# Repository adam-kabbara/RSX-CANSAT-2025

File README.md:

# RSX CanSat 2T4-2T5 Designs 

<div style="display: flex; gap: 20px; align-items: center;">

</div>
<br>

This repository is designed to manage the files made by the CanSat Team under the Robotics for Space eXploration (RSX) design team at the University of Toronto. 

**Competition Team Members:**
- Adam Kabbara | CanSat Team Lead
- Arthur Goetzke-Coburn | Mechanical Team Lead
- Daniel Yu | Electrical Team Lead
- Luke Watson | Software Team Lead
- Gianluca Ceccacci | Mechanical Team Member
- Nour Barsoum | Electrical Team Member
- Angelique Liao | Software Team Member
- Alexey Albert | Mechanical Team Member
- Robert Saab | Electrical Team Member

**CanSat Competition:**
- 📅 June 5-8, 2025
- 📍 Monterey, Virginia, United States
- 📃 [Mission document](CanSat_Mission_Guide_2025e.pdf)

**Competition Deliverables:**
- 🏆 95.87725%: [CanSat 2025 Winners](https://cansatcompetition.com/winners.html)
- 📋 Scoresheet: [TBA]()
- 💾 Mission Data: [Team #3114 Mission Data](competition_documentation/3114_mission_data_cansat_2025.csv.xlsx)
- 📝 Preliminary Design Review: [Team #3114 PDR](competition_documentation/deliverables/Cansat2025_3114_PDR.pdf)
- 🛠️ Critical Design Review: [Team #3114 CDR](competition_documentation/deliverables/Cansat2025_3114_CDR.pdf)
- 🌡️ Environemental Testing Document: [Team #3114 ENV](competition_documentation/deliverables/Cansat2025_3114_Mission_Operations_Manual.pdf)
- 🗂️ Mission Operations Manual: [Team #3114 MOM](competition_documentation/deliverables/Cansat2025_3114_Mission_Operations_Manual.pdf)
- 🛰️ Post Flight Review: [Team #3114 PFR](competition_documentation/deliverables/Cansat2025_3114_PFR.pdf)
- Note: The links above may be outdated.

**Competition Results:**
- 🗺️ 5th Place Internationally!
- 🌎 1st in North America!
- 🍁 1st in Canada!

## Folder Organization

**Calculations:**
<br> Python functions and calculations for sizing inductors and capacitors in a power electronics circuit, including formulas for inductor DC current, ripple current, peak current, and minimum capacitor value, with example calculations and printouts.

**Circuit Design:**
<br>This folder contains all the KiCad printed circuit board (PCB) designs our team has created. It also includes each PCB's related schematic, layout, and gerber files with associated custom KiCad symbols, footprints, and 3D models.

**Competition Documention:**
<br>All deliverables, team logos, and full results from the 2025 CanSat Competition in Monterey, Virginia, USA!

**Full Sensor Setup:**
<br>Initial code used to connect all payload sensor electronics together for testing before integration with full software telemetry.

**Ground Station/Telemetry Source:**
<br>Mission specific operations on payload and ground station.

**PID:**
<br>The code, notebooks, and scripts for developing, testing, and simulating PID control algorithms and sensor integration for the CanSat project.

**PFR Plots:**
<br>Contains Python scripts and output images for generating 2D and 3D plots of CanSat mission and sensor data, including GPS, altitude, and other telemetry visualizations for post-flight review and analysis.

**Sensor Testing:**
<br>All sensors used on our CanSat are tested separately using an ESP32-WROOM-32D Dev Module microcontroller. This folder contains all related information regarding the tests completed on these sensors including past designs, schematics, pin connections, and code.

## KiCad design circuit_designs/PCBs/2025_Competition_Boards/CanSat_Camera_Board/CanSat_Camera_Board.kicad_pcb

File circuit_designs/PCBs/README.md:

# 2025_Competition_Boards
This folder contains a snapshot of all the schematics, boards, and gerber files of the boards taken to the 2025 CanSat Competition.

# Final_Versions
This folder contains the entire KiCad PCB projects of all three boards inclduing improvements made after competition.

# Old_Versions
This folder contains the entire KiCad PCB projects all three boards before technical review. Most of the stitched VIAs are incorrect.

# Power_Management_Prototypes
This folder contains the KiCad projects of initial buzzer and power management board designs. All were later combined into the CanSat_Power_Management_Board.

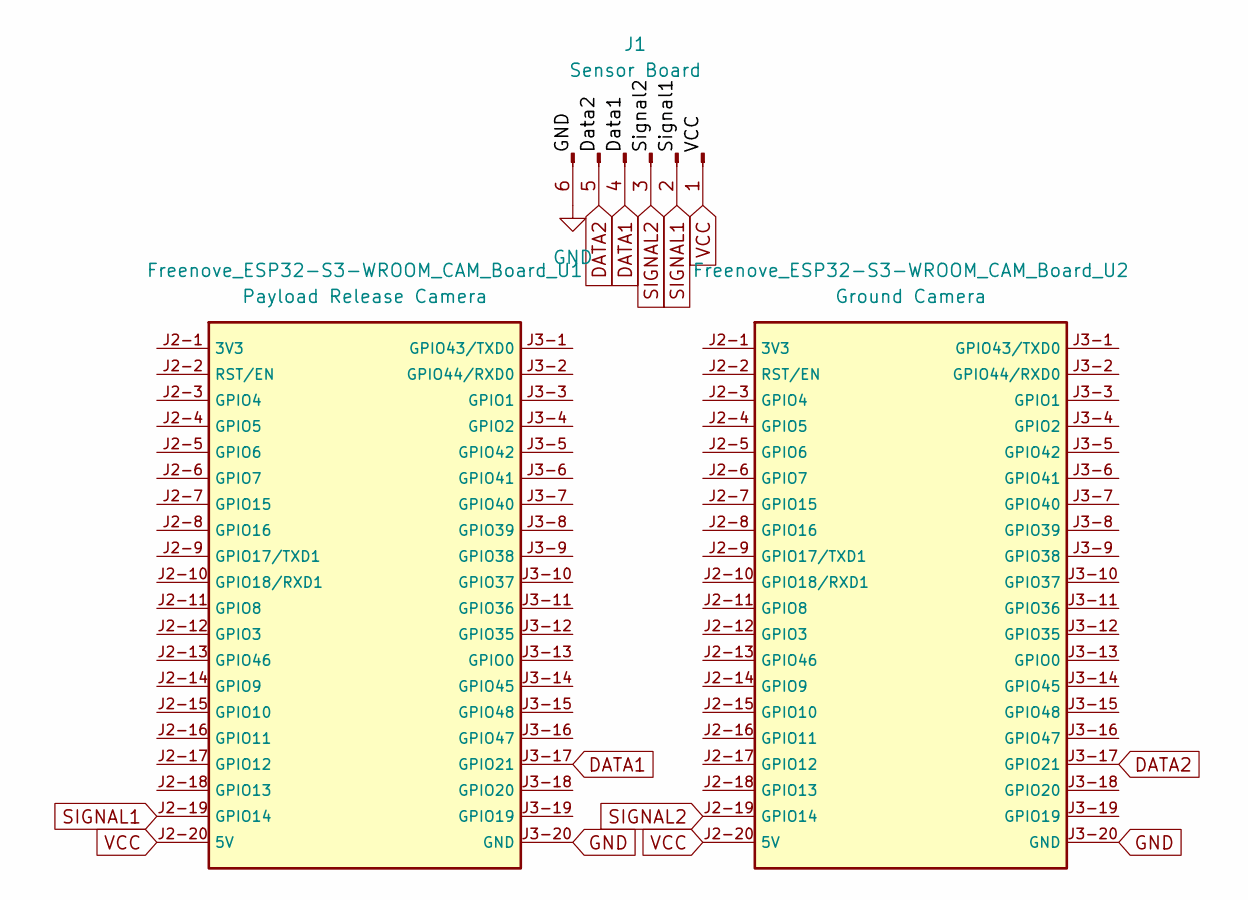
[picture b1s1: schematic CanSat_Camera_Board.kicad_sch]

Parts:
Freenove_ESP32-S3-WROOM_CAM_Board_U1: Payload Release Camera; Freenove_ESP32-S3-WROOM_CAM_Board
Freenove_ESP32-S3-WROOM_CAM_Board_U2: Ground Camera; Freenove_ESP32-S3-WROOM_CAM_Board
J1: Sensor Board; JST_PH_B6B-PH-K_1x06_P2.00mm_Vertical

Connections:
DATA1: Freenove_ESP32-S3-WROOM_CAM_Board_U1.J3-17 (GPIO21), J1.4
DATA2: Freenove_ESP32-S3-WROOM_CAM_Board_U2.J3-17 (GPIO21), J1.5
GND: Freenove_ESP32-S3-WROOM_CAM_Board_U1.J3-20 (GND), Freenove_ESP32-S3-WROOM_CAM_Board_U2.J3-20 (GND), J1.6
SIGNAL1: Freenove_ESP32-S3-WROOM_CAM_Board_U1.J2-19 (GPIO14), J1.2
SIGNAL2: Freenove_ESP32-S3-WROOM_CAM_Board_U2.J2-19 (GPIO14), J1.3
VCC: Freenove_ESP32-S3-WROOM_CAM_Board_U1.J2-20 (5V), Freenove_ESP32-S3-WROOM_CAM_Board_U2.J2-20 (5V), J1.1

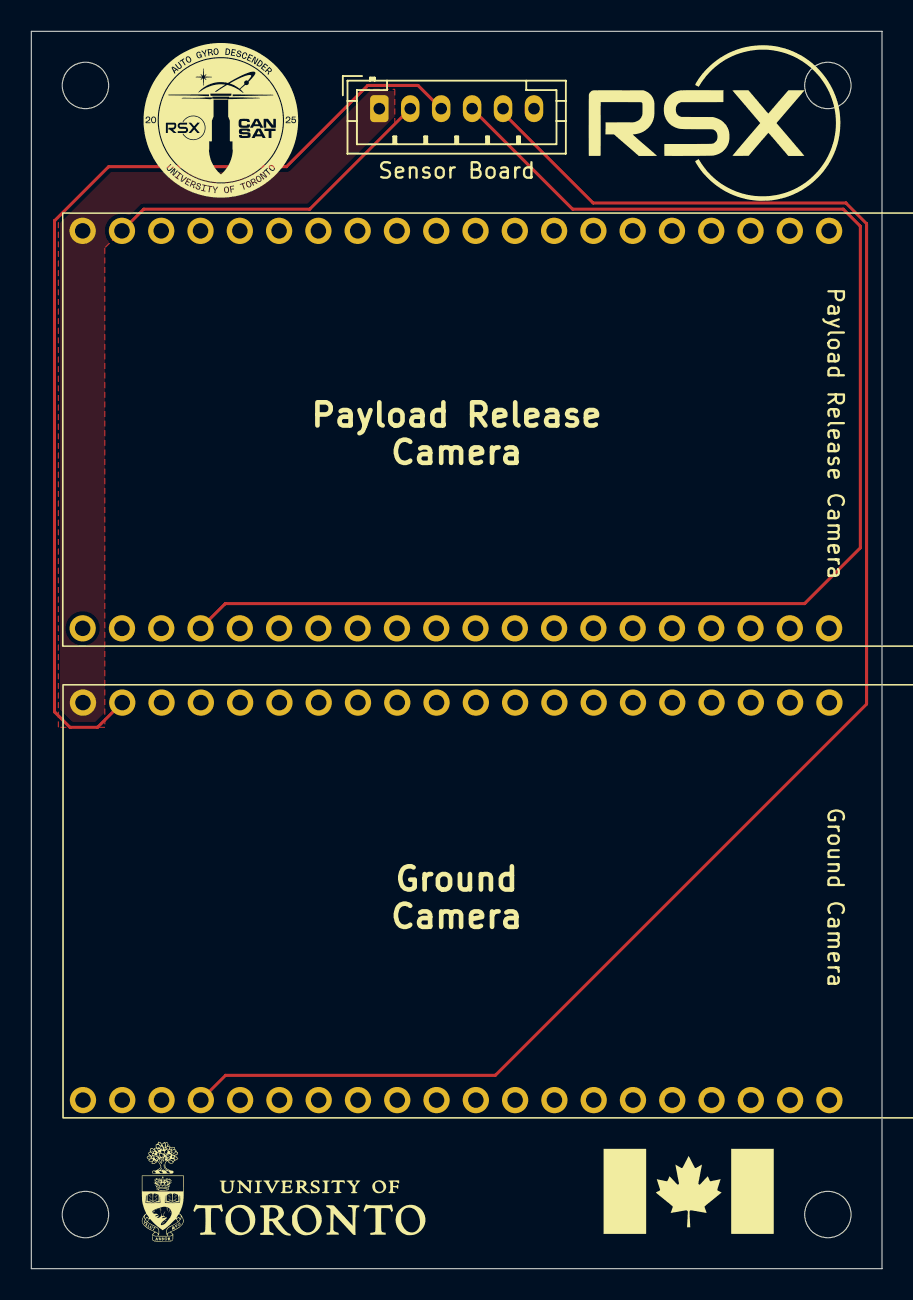
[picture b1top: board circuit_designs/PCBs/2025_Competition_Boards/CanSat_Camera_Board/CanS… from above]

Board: 2 copper layers, 55.0 x 80.0 mm, 3 parts (0 on the bottom side), 6 nets.

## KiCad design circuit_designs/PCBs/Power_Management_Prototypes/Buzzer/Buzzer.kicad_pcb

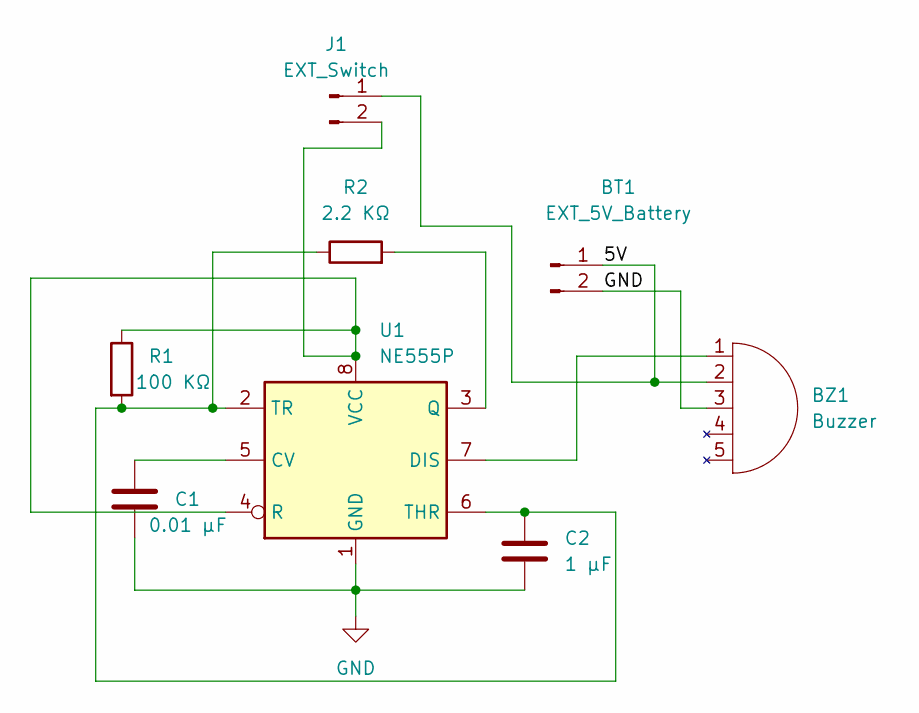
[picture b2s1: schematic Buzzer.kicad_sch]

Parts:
BT1: EXT_5V_Battery; External_Connection_2pin
BZ1: Buzzer; Buzzer_Connection
C1: 0.01 μF; CP_Axial_L11.0mm_D5.0mm_P18.00mm_Horizontal
C2: 1 μF; CP_Axial_L10.0mm_D6.0mm_P15.00mm_Horizontal
J1: EXT_Switch; External_Connection_2pin
R1: 100 KΩ; R_Axial_DIN0207_L6.3mm_D2.5mm_P10.16mm_Horizontal
R2: 2.2 KΩ; R_Axial_DIN0207_L6.3mm_D2.5mm_P10.16mm_Horizontal
U1: NE555P; DIP-8_W7.62mm

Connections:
/5V: BT1.1, BZ1.2 (5V), J1.1
GND: BT1.2, BZ1.3 (G), C1.2, C2.2, U1.1 (GND)
unnamed: BZ1.1 (Aux), U1.7 (DIS)
unnamed: J1.2, R1.1, U1.4 (R), U1.8 (VCC)
unnamed: C1.1, U1.5 (CV)
unnamed: R2.2, U1.3 (Q)
unnamed: C2.1, R1.2, R2.1, U1.2 (TR), U1.6 (THR)

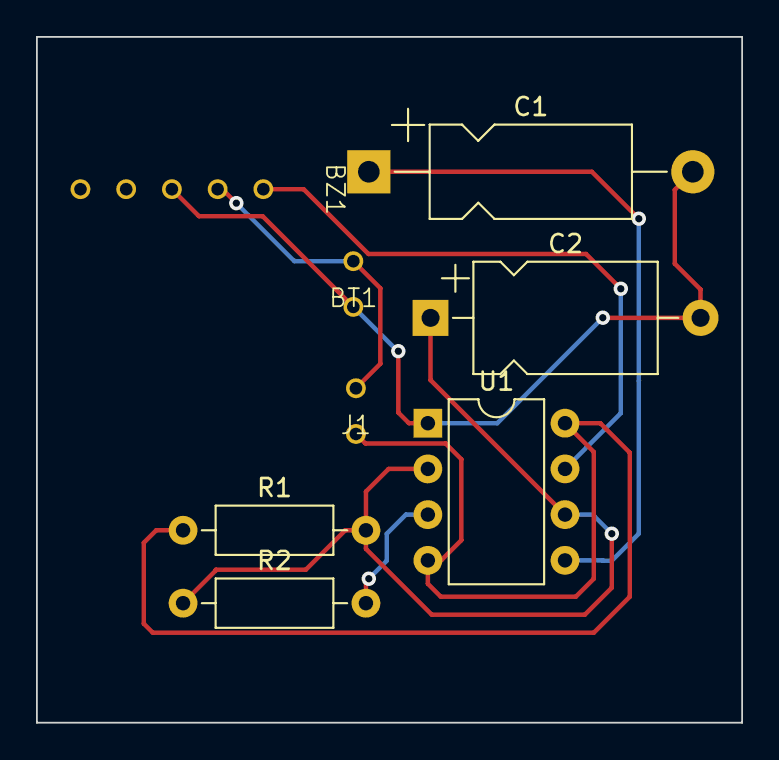
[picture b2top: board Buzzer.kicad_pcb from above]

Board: 2 copper layers, 39.2 x 38.1 mm, 8 parts (0 on the bottom side), 7 nets.

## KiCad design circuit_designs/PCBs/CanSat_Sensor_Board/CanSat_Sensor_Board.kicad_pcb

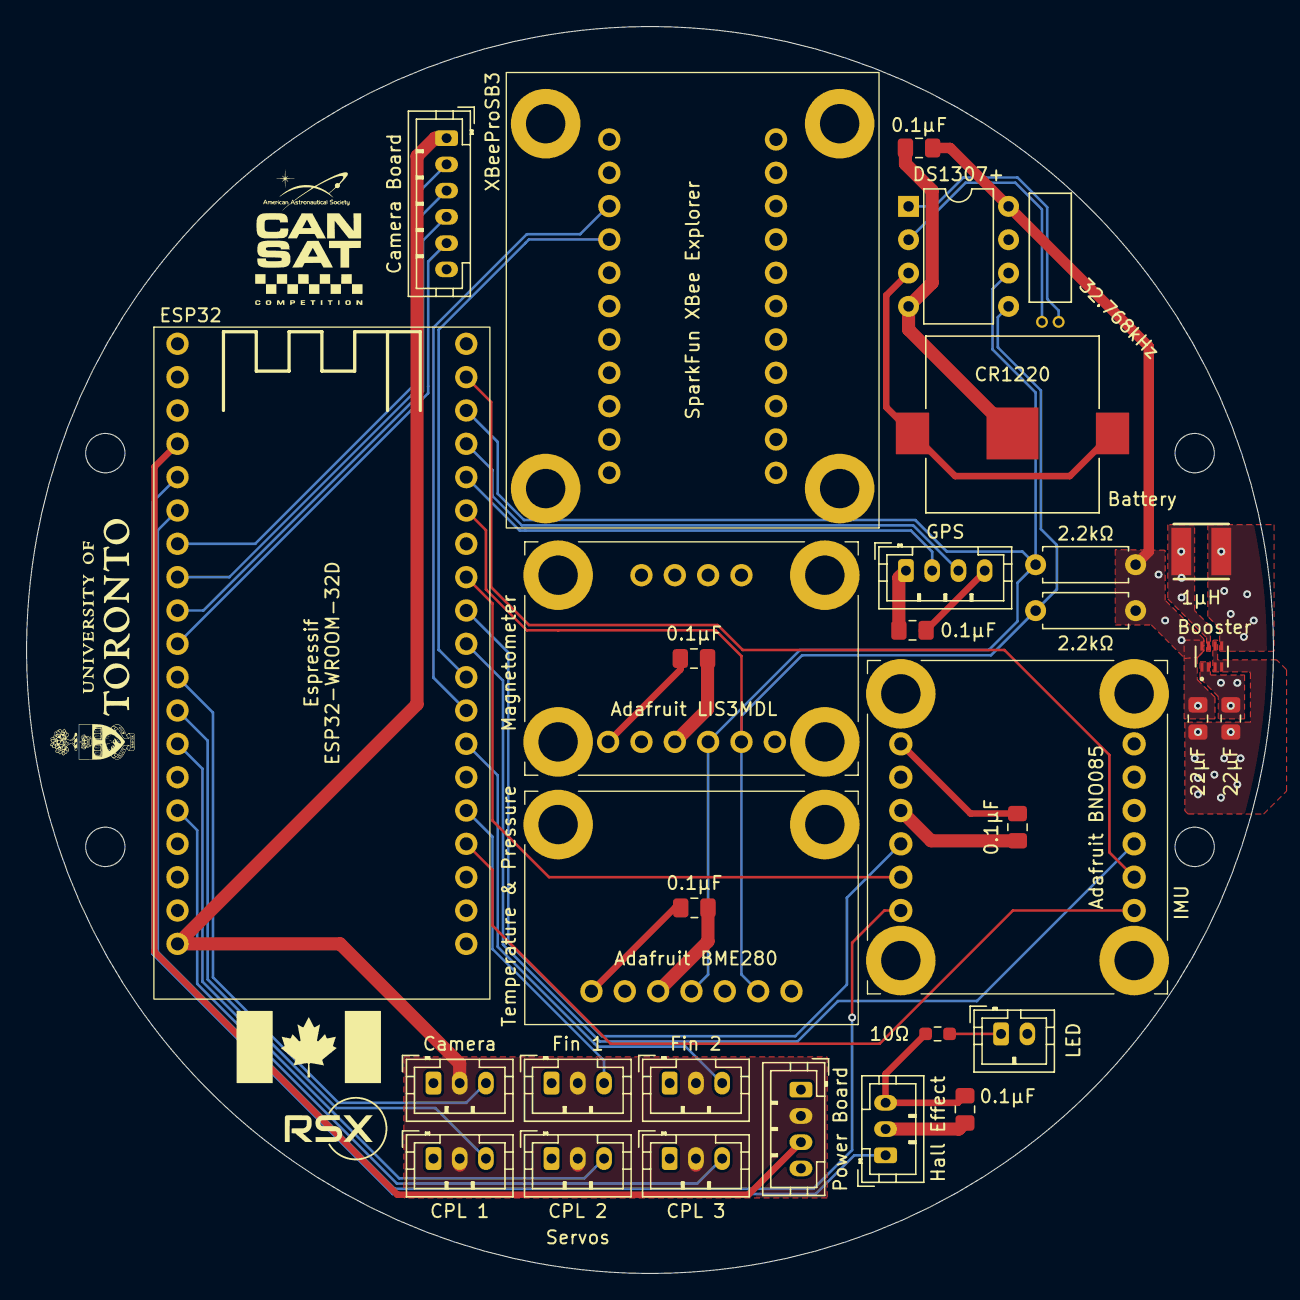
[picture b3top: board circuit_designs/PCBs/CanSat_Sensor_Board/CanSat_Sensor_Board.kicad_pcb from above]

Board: 4 copper layers, 95.0 x 95.0 mm, 32 parts (0 on the bottom side), 33 nets.

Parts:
2894TR_U7: Battery; BAT_2894TR
Adafruit_BME280_STEMMA_QT_U3: Temperature & Pressure; Adafruit_BME280_STEMMA_QT
Adafruit_BNO085_U5: IMU; Adafruit_BNO085
Adafruit_LIS3MDL_U4: Magnetometer; Adafruit_LIS3MDL
C1, C2, C3, C4, C5, C6: 0.1μF; C_0805_2012Metric_Pad1.18x1.45mm_HandSolder
C7, C8: 22μF; C_0805_2012Metric_Pad1.18x1.45mm_HandSolder
DS1307+_U6: DS1307+; DIP-8_W7.62mm
ESP32-DEVKIT-32_U1: ESP32; ESP32-WROOM-32D_Dev_Board
J1: Power Board; JST_PH_B4B-PH-K_1x04_P2.00mm_Vertical
J2: Camera Board; JST_PH_B6B-PH-K_1x06_P2.00mm_Vertical
J3: Hall Effect; JST_PH_B3B-PH-K_1x03_P2.00mm_Vertical
J4: GPS; JST_PH_B4B-PH-K_1x04_P2.00mm_Vertical
J5: LED; JST_PH_B2B-PH-K_1x02_P2.00mm_Vertical
J6: Fin 1; JST_PH_B3B-PH-K_1x03_P2.00mm_Vertical
J7: Fin 2; JST_PH_B3B-PH-K_1x03_P2.00mm_Vertical
J8: Camera; JST_PH_B3B-PH-K_1x03_P2.00mm_Vertical
J9: CPL 1; JST_PH_B3B-PH-K_1x03_P2.00mm_Vertical
J10: CPL 2; JST_PH_B3B-PH-K_1x03_P2.00mm_Vertical
J11: CPL 3; JST_PH_B3B-PH-K_1x03_P2.00mm_Vertical
R1: 10Ω; R_0603_1608Metric_Pad0.98x0.95mm_HandSolder
R2, R3: 2.2kΩ; R_Axial_DIN0207_L6.3mm_D2.5mm_P7.62mm_Horizontal
SparkFunXBeeExplorer_U2: XBeeProSB3; SparkFun_XBee_Explorer_Regulated
TPS610333DRLR_U8: Booster; SOT-5X3-8_DRL_TEX
WE-LQS_4025_L1: 1μH; WE-LQS_4025
Y1: 32.768kHz; XTAL_AB38T-32.768KHZ

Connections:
/3.3V: Adafruit_BME280_STEMMA_QT_U3.1, Adafruit_BNO085_U5.JP1_1 (VIN), Adafruit_LIS3MDL_U4.1, C1.2, C2.1, C3.2, C4.2, C5.2, C7.2, J1.1, J3.3, J4.4, R1.2, SparkFunXBeeExplorer_U2.JP5_10 (3.3V), TPS610333DRLR_U8.1 (VIN), TPS610333DRLR_U8.2 (EN), TPS610333DRLR_U8.5 (FB), WE-LQS_4025_L1.1
/5V: C6.2, C8.1, DS1307+_U6.8 (VCC), R2.1, R3.1, TPS610333DRLR_U8.8 (VOUT)
/7.4V: ESP32-DEVKIT-32_U1.J2-19 (EXT_5V), J1.2, J2.1, J6.2, J7.2, J8.2, J9.2, J10.2, J11.2
/ADC: ESP32-DEVKIT-32_U1.J2-4 (SENSOR_VN), J1.3
/SW: TPS610333DRLR_U8.7 (SW), WE-LQS_4025_L1.2
GND: 2894TR_U7.N, Adafruit_BME280_STEMMA_QT_U3.3, Adafruit_BNO085_U5.JP1_3 (GND), Adafruit_LIS3MDL_U4.3, C1.1, C2.2, C3.1, C4.1, C5.1, C6.1, C7.1, C8.2, DS1307+_U6.4 (GND), ESP32-DEVKIT-32_U1.J2-14 (GND1), ESP32-DEVKIT-32_U1.J3-1 (GND3), ESP32-DEVKIT-32_U1.J3-7 (GND2), J1.4, J2.6, J3.2, J4.1, J5.2, J6.1, J7.1, J8.1, J9.1, J10.1, J11.1, SparkFunXBeeExplorer_U2.JP5_1 (GND), SparkFunXBeeExplorer_U2.JP5_11 (GND), TPS610333DRLR_U8.3 (MODE), TPS610333DRLR_U8.4 (PG), TPS610333DRLR_U8.6 (GND)
unnamed: Adafruit_BME280_STEMMA_QT_U3.4, Adafruit_LIS3MDL_U4.4, DS1307+_U6.6 (SCL), ESP32-DEVKIT-32_U1.J3-3 (IO22), R3.2
unnamed: Adafruit_BME280_STEMMA_QT_U3.6, Adafruit_LIS3MDL_U4.5, DS1307+_U6.5 (SDA), ESP32-DEVKIT-32_U1.J3-6 (IO21), R2.2
unnamed: Adafruit_BNO085_U5.JP2_6 (CS), ESP32-DEVKIT-32_U1.J3-16 (IO15)
unnamed: Adafruit_BNO085_U5.JP2_5 (DI), ESP32-DEVKIT-32_U1.J3-2 (IO23)
unnamed: Adafruit_BNO085_U5.JP1_4 (SCL), ESP32-DEVKIT-32_U1.J3-9 (IO18)
unnamed: Adafruit_BNO085_U5.JP1_5 (SDA), ESP32-DEVKIT-32_U1.J3-8 (IO19)
unnamed: Adafruit_BNO085_U5.JP1_6 (~INT), ESP32-DEVKIT-32_U1.J2-6 (IO35)
unnamed: Adafruit_BNO085_U5.JP2_4 (~RST), ESP32-DEVKIT-32_U1.J3-10 (IO5)
unnamed: 2894TR_U7.P1, 2894TR_U7.P2, DS1307+_U6.3 (VBAT)
unnamed: DS1307+_U6.1 (X1), Y1.1
unnamed: DS1307+_U6.2 (X2), Y1.2
unnamed: ESP32-DEVKIT-32_U1.J3-15 (IO2), J6.3
unnamed: ESP32-DEVKIT-32_U1.J3-13 (IO4), J7.3
unnamed: ESP32-DEVKIT-32_U1.J2-13 (IO12), J10.3
unnamed: ESP32-DEVKIT-32_U1.J2-15 (IO13), J11.3
unnamed: ESP32-DEVKIT-32_U1.J2-12 (IO14), J9.3
unnamed: ESP32-DEVKIT-32_U1.J3-12 (IO16), SparkFunXBeeExplorer_U2.JP5_9 (DOUT)
unnamed: ESP32-DEVKIT-32_U1.J3-11 (IO17), SparkFunXBeeExplorer_U2.JP5_8 (DIN)
unnamed: ESP32-DEVKIT-32_U1.J2-9 (IO25), J2.4
unnamed: ESP32-DEVKIT-32_U1.J2-10 (IO26), J2.5
unnamed: ESP32-DEVKIT-32_U1.J2-11 (IO27), J8.3
unnamed: ESP32-DEVKIT-32_U1.J2-7 (IO32), J2.2
unnamed: ESP32-DEVKIT-32_U1.J2-8 (IO33), J2.3
unnamed: ESP32-DEVKIT-32_U1.J2-5 (IO34), J3.1
unnamed: ESP32-DEVKIT-32_U1.J3-5 (RXD0), J4.2
unnamed: ESP32-DEVKIT-32_U1.J3-4 (TXD0), J4.3
unnamed: J5.1, R1.1

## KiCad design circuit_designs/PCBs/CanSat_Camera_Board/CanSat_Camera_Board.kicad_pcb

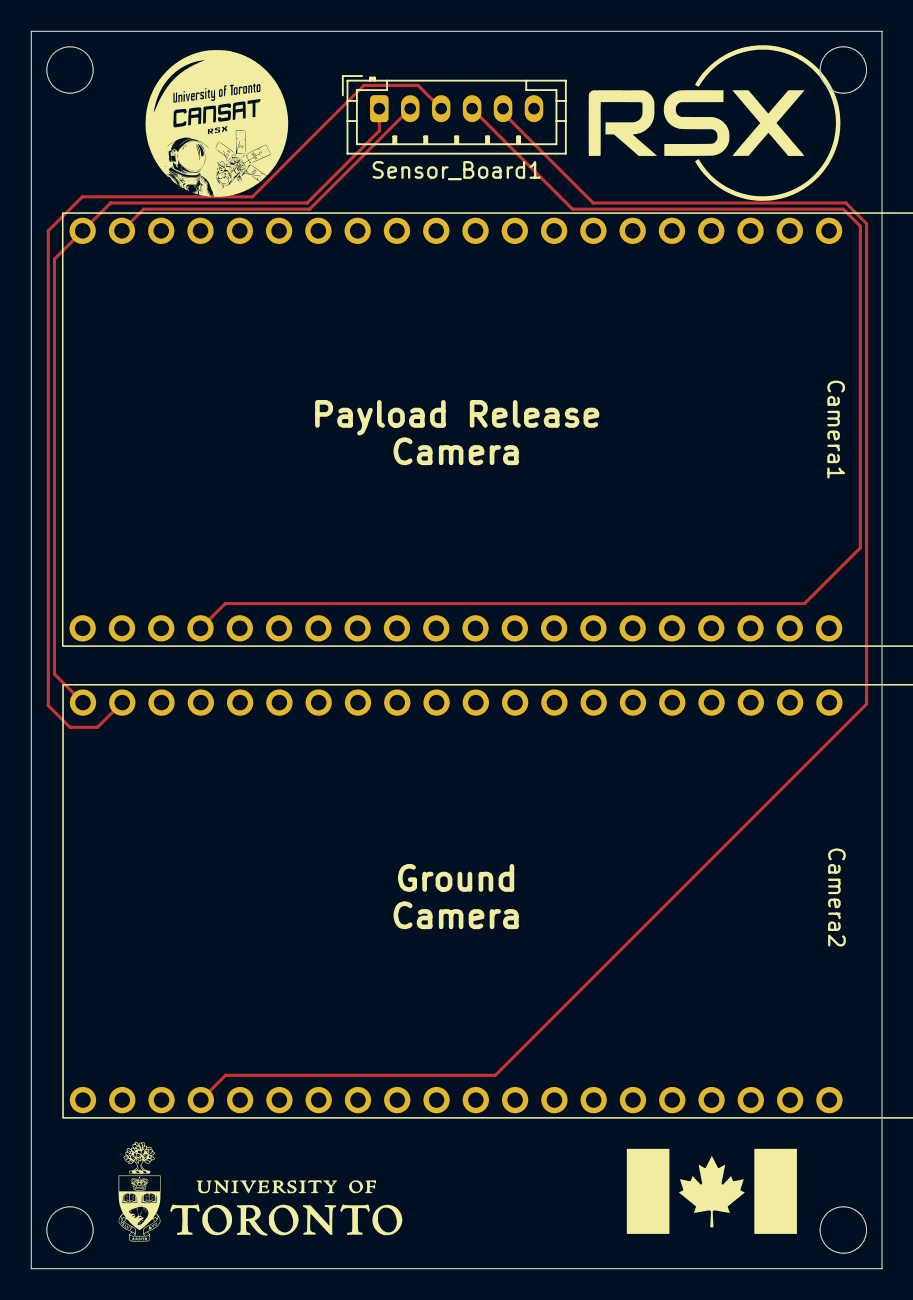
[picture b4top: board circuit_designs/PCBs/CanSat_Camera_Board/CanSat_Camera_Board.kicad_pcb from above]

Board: 2 copper layers, 55.0 x 80.0 mm, 3 parts (0 on the bottom side), 6 nets.

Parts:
Camera1, Camera2: Freenove_ESP32-S3-WROOM_CAM_Board
Sensor_Board1: Conn_01x06_Pin; JST_PH_B6B-PH-K_1x06_P2.00mm_Vertical

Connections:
DATA1: Camera1.J3-17 (GPIO21), Sensor_Board1.4
DATA2: Camera2.J3-17 (GPIO21), Sensor_Board1.5
GND: Camera1.J3-20 (GND), Camera2.J3-20 (GND), Sensor_Board1.6
SIGNAL1: Camera1.J2-19 (GPIO14), Sensor_Board1.2
SIGNAL2: Camera2.J2-19 (GPIO14), Sensor_Board1.3
VCC: Camera1.J2-20 (5V), Camera2.J2-20 (5V), Sensor_Board1.1

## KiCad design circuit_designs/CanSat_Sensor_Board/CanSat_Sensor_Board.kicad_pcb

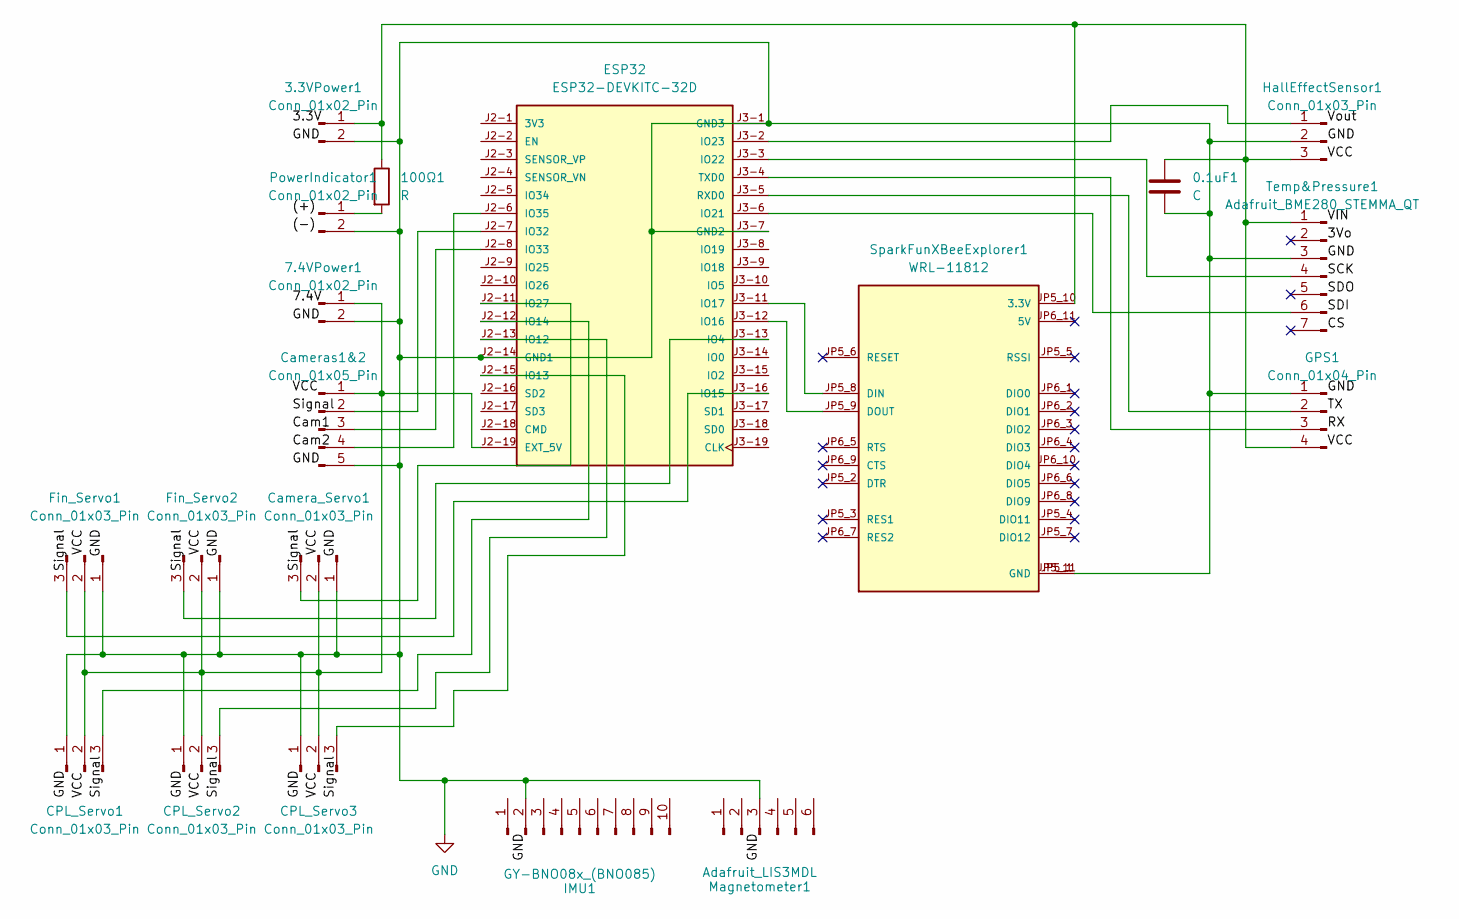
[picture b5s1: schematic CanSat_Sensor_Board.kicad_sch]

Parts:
0.1uF1: C; C_0201_0603Metric_Pad0.64x0.40mm_HandSolder
3.3VPower1, 7.4VPower1: Conn_01x02_Pin; JST_PH_B2B-PH-K_1x02_P2.00mm_Vertical
100Ω1: R; R_Axial_DIN0207_L6.3mm_D2.5mm_P7.62mm_Horizontal
CPL_Servo1, CPL_Servo2, CPL_Servo3: Conn_01x03_Pin; JST_PH_B3B-PH-K_1x03_P2.00mm_Vertical
Camera_Servo1: Conn_01x03_Pin; JST_PH_B3B-PH-K_1x03_P2.00mm_Vertical
Cameras1&2: Conn_01x05_Pin; JST_PH_B5B-PH-K_1x05_P2.00mm_Vertical
ESP32: ESP32-DEVKITC-32D; MODULE_ESP32-DEVKITC-32D; PARTREV V4
Fin_Servo1, Fin_Servo2: Conn_01x03_Pin; JST_PH_B3B-PH-K_1x03_P2.00mm_Vertical
GPS1: Conn_01x04_Pin; JST_PH_B4B-PH-K_1x04_P2.00mm_Vertical
HallEffectSensor1: Conn_01x03_Pin; JST_PH_B3B-PH-K_1x03_P2.00mm_Vertical
IMU1: GY-BNO08x_(BNO085)
Magnetometer1: Adafruit_LIS3MDL
PowerIndicator1: Conn_01x02_Pin; JST_PH_B2B-PH-K_1x02_P2.00mm_Vertical
SparkFunXBeeExplorer1: WRL-11812; MODULE_WRL-11812; PARTREV v21
Temp&Pressure1: Adafruit_BME280_STEMMA_QT

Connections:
GND: 0.1uF1.2, 3.3VPower1.2, 7.4VPower1.2, CPL_Servo1.1, CPL_Servo2.1, CPL_Servo3.1, Camera_Servo1.1, Cameras1&2.5, ESP32.J2-14 (GND1), ESP32.J3-1 (GND3), ESP32.J3-7 (GND2), Fin_Servo1.1, Fin_Servo2.1, GPS1.1, HallEffectSensor1.2, IMU1.2, Magnetometer1.3, PowerIndicator1.2, SparkFunXBeeExplorer1.JP5_1 (GND), SparkFunXBeeExplorer1.JP5_11 (GND), Temp&Pressure1.3
unnamed: 0.1uF1.1, 3.3VPower1.1, 100Ω1.1, GPS1.4, HallEffectSensor1.3, SparkFunXBeeExplorer1.JP5_10 (3.3V), Temp&Pressure1.1
unnamed: 7.4VPower1.1, CPL_Servo1.2, CPL_Servo2.2, CPL_Servo3.2, Camera_Servo1.2, Cameras1&2.1, ESP32.J2-19 (EXT_5V), Fin_Servo1.2, Fin_Servo2.2
unnamed: CPL_Servo1.3, ESP32.J2-12 (IO14)
unnamed: CPL_Servo2.3, ESP32.J2-13 (IO12)
unnamed: CPL_Servo3.3, ESP32.J2-15 (IO13)
unnamed: Camera_Servo1.3, ESP32.J2-11 (IO27)
unnamed: Cameras1&2.2, ESP32.J2-7 (IO32)
unnamed: Cameras1&2.3, ESP32.J2-8 (IO33)
unnamed: Cameras1&2.4, ESP32.J2-6 (IO35)
unnamed: ESP32.J3-13 (IO4), Fin_Servo2.3
unnamed: ESP32.J3-16 (IO15), Fin_Servo1.3
unnamed: ESP32.J3-12 (IO16), SparkFunXBeeExplorer1.JP5_9 (DOUT)
unnamed: ESP32.J3-11 (IO17), SparkFunXBeeExplorer1.JP5_8 (DIN)
unnamed: ESP32.J3-6 (IO21), Temp&Pressure1.6
unnamed: ESP32.J3-3 (IO22), Temp&Pressure1.4
unnamed: ESP32.J3-2 (IO23), HallEffectSensor1.1
unnamed: ESP32.J3-5 (RXD0), GPS1.2
unnamed: ESP32.J3-4 (TXD0), GPS1.3
unnamed: 100Ω1.2, PowerIndicator1.1

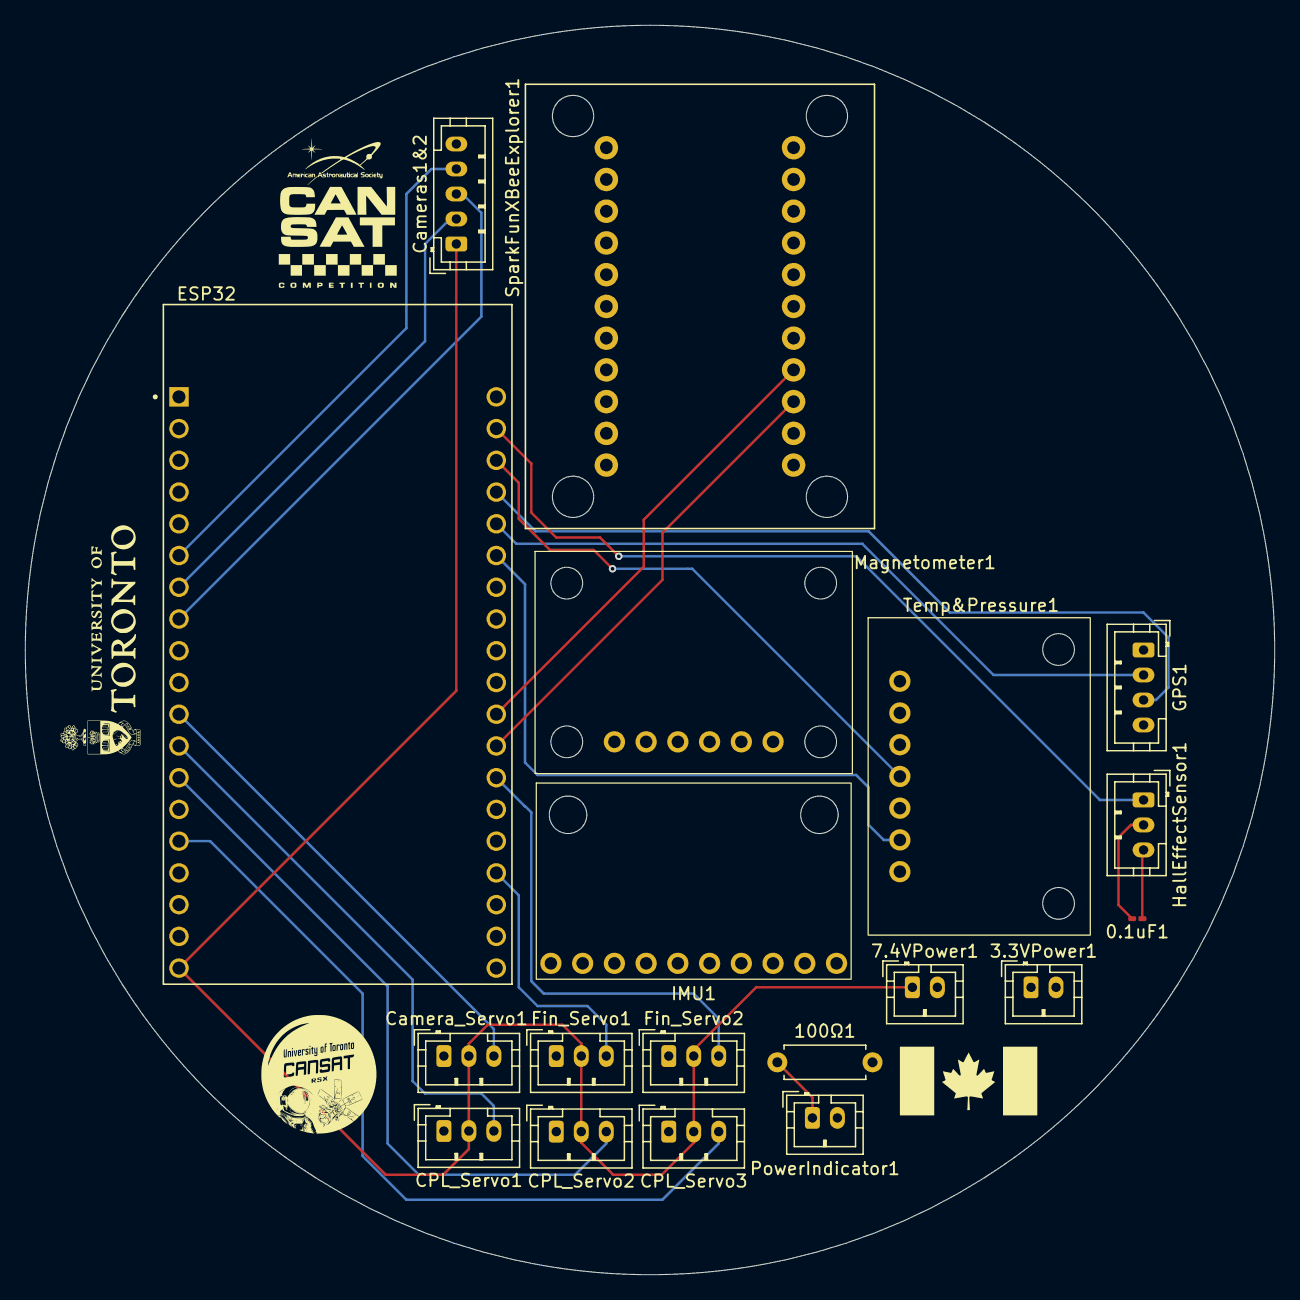
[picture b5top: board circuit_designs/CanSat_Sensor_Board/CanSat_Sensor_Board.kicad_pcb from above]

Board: 4 copper layers, 100.0 x 100.0 mm, 19 parts (0 on the bottom side), 20 nets.

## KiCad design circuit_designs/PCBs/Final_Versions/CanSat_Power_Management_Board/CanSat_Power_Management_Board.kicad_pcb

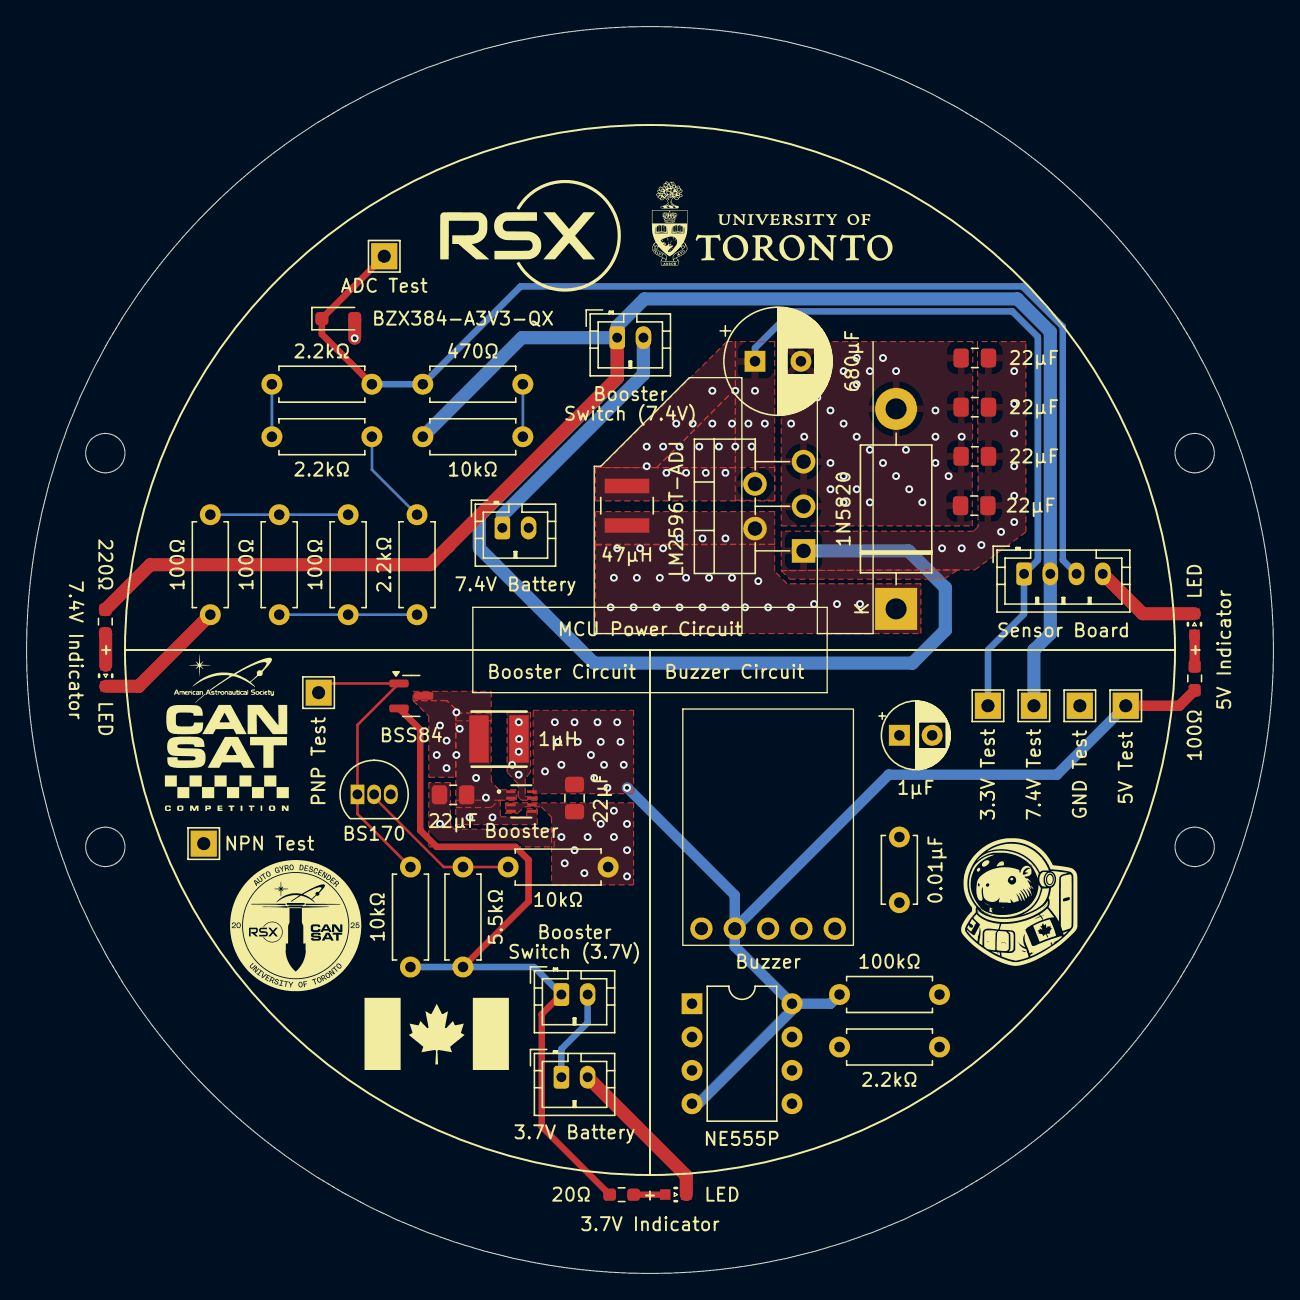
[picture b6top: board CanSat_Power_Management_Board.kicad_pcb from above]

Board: 4 copper layers, 95.0 x 95.0 mm, 50 parts (0 on the bottom side), 25 nets.

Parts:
ASPI-4030S-470M-T_L1: 47μH; IND_ASPI-4030S-470M-T
BZ1: Buzzer; Matek_Lost_Model_Beeper
C6, C7: 22μF; C_0805_2012Metric_Pad1.18x1.45mm_HandSolder
C8: 0.01μF; C_Disc_D5.0mm_W2.5mm_P5.00mm
C9: 1μF; CP_Radial_D5.0mm_P2.50mm
Cin1, Cin2, Cin3, Cin4: 22μF; C_0805_2012Metric_Pad1.18x1.45mm_HandSolder
Cout5: 680μF; CP_Radial_D8.0mm_P3.50mm
D1: 1N5820; D_DO-201AD_P15.24mm_Horizontal
D2: BZX384-A3V3-QX; D_SOD-323_HandSoldering
D3: LED (3.7V); WL-SMCW_0603
D4: LED (5V); WL-SMCW_0603
D5: LED (7.4V); WL-SMCW_0603
J1: MCU Switch (7.4V); JST_PH_B2B-PH-K_1x02_P2.00mm_Vertical
J2: 7.4V Battery; JST_PH_B2B-PH-K_1x02_P2.00mm_Vertical
J3: Sensor Board; JST_PH_B4B-PH-K_1x04_P2.00mm_Vertical
J4: Booster Switch (3.7V); JST_PH_B2B-PH-K_1x02_P2.00mm_Vertical
J5: 3.7V Battery; JST_PH_B2B-PH-K_1x02_P2.00mm_Vertical
Q1: BS170; TO-92_Inline
Q2: BSS84; SOT-23
R1, R2, R3: 100Ω; R_Axial_DIN0207_L6.3mm_D2.5mm_P7.62mm_Horizontal
R4, R5, R6, R13: 2.2kΩ; R_Axial_DIN0207_L6.3mm_D2.5mm_P7.62mm_Horizontal
R7: 470Ω; R_Axial_DIN0207_L6.3mm_D2.5mm_P7.62mm_Horizontal
R8, R10, R11: 10kΩ; R_Axial_DIN0207_L6.3mm_D2.5mm_P7.62mm_Horizontal
R9: 5.5kΩ; R_Axial_DIN0207_L6.3mm_D2.5mm_P7.62mm_Horizontal
R12: 100kΩ; R_Axial_DIN0207_L6.3mm_D2.5mm_P7.62mm_Horizontal
R14: 20Ω; R_0603_1608Metric_Pad0.98x0.95mm_HandSolder
R15: 100Ω; R_0603_1608Metric_Pad0.98x0.95mm_HandSolder
R16: 220Ω; R_0603_1608Metric_Pad0.98x0.95mm_HandSolder
TP1: ADC Test; TestPoint_THTPad_2.0x2.0mm_Drill1.0mm
TP2: 7.4V Test; TestPoint_THTPad_2.0x2.0mm_Drill1.0mm
TP3: 3.3V Test; TestPoint_THTPad_2.0x2.0mm_Drill1.0mm
TP4: 5V Test; TestPoint_THTPad_2.0x2.0mm_Drill1.0mm
TP5: NPN Test; TestPoint_THTPad_2.0x2.0mm_Drill1.0mm
TP6: PNP Test; TestPoint_THTPad_2.0x2.0mm_Drill1.0mm
TP7: GND Test; TestPoint_THTPad_2.0x2.0mm_Drill1.0mm
TPS610333DRLR_U2: Booster; SOT-5X3-8_DRL_TEX
U1: LM2596T-ADJ; TO-220-5_P3.4x3.7mm_StaggerOdd_Lead3.8mm_Vertical
U3: NE555P; DIP-8_W7.62mm
WE-LQS_4025_L2: 1μH; WE-LQS_4025

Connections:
3.3V: ASPI-4030S-470M-T_L1.2, Cout5.1, J3.1, TP3.1, U1.4 (FB)
7.4V: Cin1.1, Cin2.1, Cin3.1, Cin4.1, J1.1, J3.2, R8.2, R16.2, TP2.1, U1.1 (VIN)
/5V: BZ1.2 (5V), C7.1, R12.1, R15.2, TP4.1, TPS610333DRLR_U2.8 (VOUT), U3.4 (R), U3.8 (VCC)
/OUT: ASPI-4030S-470M-T_L1.1, D1.1 (K), U1.2 (OUT)
/SW: TPS610333DRLR_U2.7 (SW), WE-LQS_4025_L2.2
/VIN: C6.1, Q2.3 (D), TPS610333DRLR_U2.1 (VIN), TPS610333DRLR_U2.2 (EN), TPS610333DRLR_U2.5 (FB), WE-LQS_4025_L2.1
ADC: D2.1 (K), J3.3, R6.2, R7.1, TP1.1
GND: BZ1.3 (G), C6.2, C7.2, C8.2, C9.2, Cin1.2, Cin2.2, Cin3.2, Cin4.2, Cout5.2, D1.2 (A), D2.2 (A), D3.1 (K), D4.1 (K), D5.1 (K), J2.2, J3.4, J5.2, Q1.3 (S), R1.2, R10.2, TP7.1, TPS610333DRLR_U2.3 (MODE), TPS610333DRLR_U2.4 (PG), TPS610333DRLR_U2.6 (GND), U1.3 (GND), U1.5 (~ON/OFF), U3.1 (GND)
unnamed: BZ1.1 (Aux), U3.7 (DIS)
unnamed: D3.2 (A), R14.1
unnamed: D4.2 (A), R15.1
unnamed: D5.2 (A), R16.1
unnamed: J1.2, J2.1
unnamed: J4.1, Q2.2 (S), R9.1, R11.1, R14.2
unnamed: J4.2, J5.1
unnamed: Q1.1 (D), Q2.1 (G), R11.2, TP6.1
unnamed: Q1.2 (G), R9.2, R10.1, TP5.1
unnamed: R1.1, R2.2, R3.2
unnamed: R2.1, R3.1, R4.1
unnamed: R4.2, R5.1
unnamed: R5.2, R6.1
unnamed: R7.2, R8.1
unnamed: C8.1, U3.5 (CV)
unnamed: R13.2, U3.3 (Q)
unnamed: C9.1, R12.2, R13.1, U3.2 (TR), U3.6 (THR)

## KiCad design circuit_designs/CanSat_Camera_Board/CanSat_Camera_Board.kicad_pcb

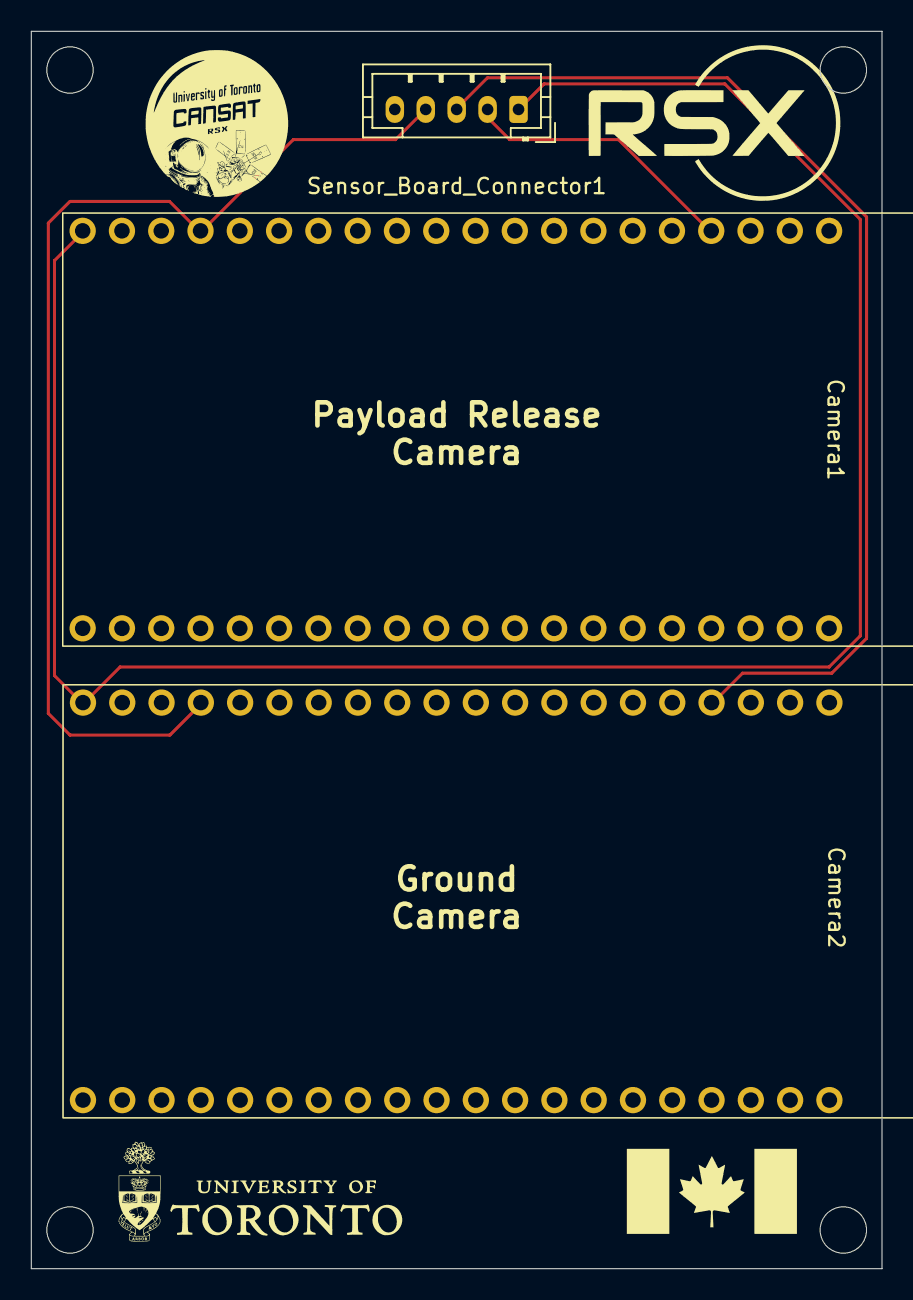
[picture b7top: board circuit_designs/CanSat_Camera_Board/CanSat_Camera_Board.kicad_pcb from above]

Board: 2 copper layers, 55.0 x 80.0 mm, 3 parts (0 on the bottom side), 5 nets.

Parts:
Camera1, Camera2: Freenove_ESP32-S3-WROOM_CAM_Board
Sensor_Board_Connector1: Conn_01x05_Pin; JST_PH_B5B-PH-K_1x05_P2.00mm_Vertical

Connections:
CAM1: Camera1.J2-4 (GPIO5), Sensor_Board_Connector1.2
CAM2: Camera2.J2-4 (GPIO5), Sensor_Board_Connector1.3
GND: Camera1.J3-20 (GND), Camera2.J3-20 (GND), Sensor_Board_Connector1.5
SIG1: Camera1.J2-17 (GPIO12), Camera2.J2-17 (GPIO12), Sensor_Board_Connector1.4
VCC: Camera1.J2-20 (5V), Camera2.J2-20 (5V), Sensor_Board_Connector1.1
